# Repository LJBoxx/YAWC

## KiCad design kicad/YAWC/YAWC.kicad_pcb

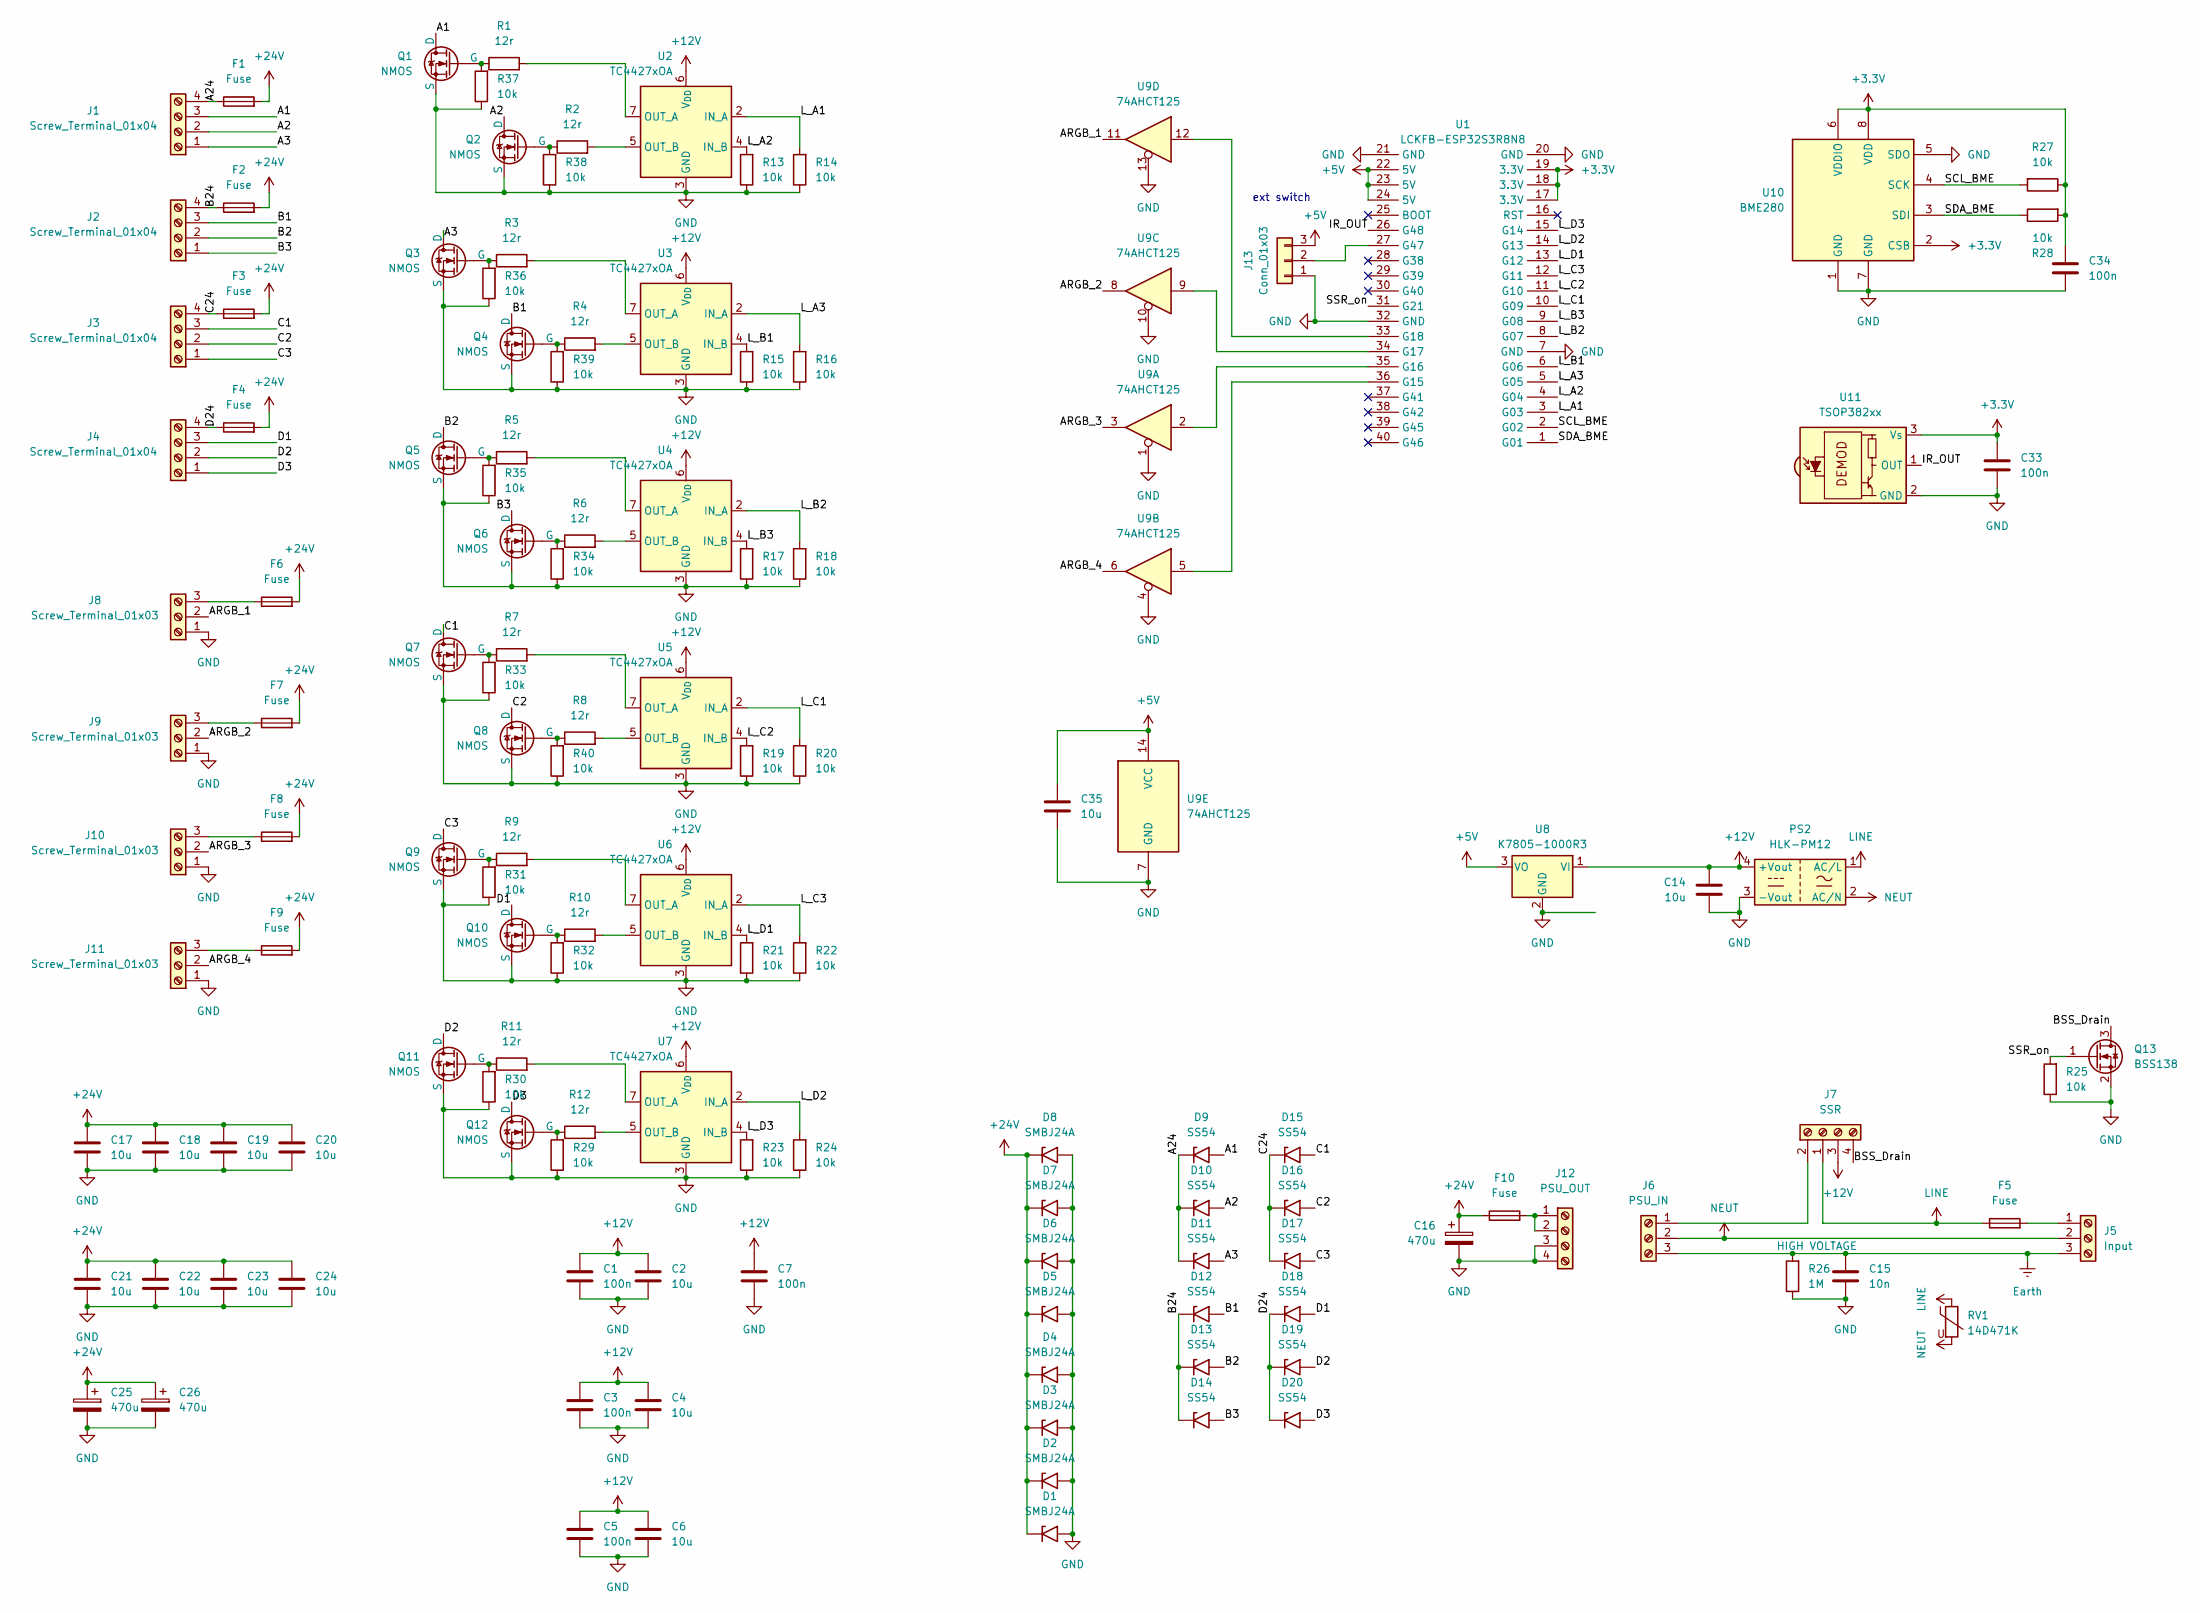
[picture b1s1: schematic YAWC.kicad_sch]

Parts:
C1, C3, C5, C7, C33, C34: 100n; C_0603_1608Metric; LCSC C1591
C2, C4, C6, C14, C17, C18, C19, C20, C21, C22, C23, C24, C35: 10u; C_1210_3225Metric; LCSC C138687
C15: 10n; C_Rect_L13.0mm_W4.0mm_P10.00mm_FKS3_FKP3_MKS4; LCSC C428926
C16, C25, C26: 470u; CP_Radial_D10.0mm_P5.00mm; LCSC C3038120
D1, D2, D3, D4, D5, D6, D7, D8: SMBJ24A; D_SMB; LCSC C224017
D9, D10, D11, D12, D13, D14, D15, D16, D17, D18, D19, D20: SS54; D_SMB; LCSC C22452
F1, F2, F3, F4, F6, F7, F8, F9, F10: Fuse; FUSE-TH_4P-L16.0-W6.7; LCSC C19727305
F5: Fuse; Fuse_Bourns_MF-SM_9.5x6.71mm; LCSC C108518
J1, J2, J3, J4: Screw_Terminal_01x04; TerminalBlock_bornier-4_P5.08mm; LCSC C2915641
J5: Input; TerminalBlock_bornier-3_P5.08mm; LCSC C72334
J6: PSU_IN; TerminalBlock_bornier-3_P5.08mm; LCSC C72334
J7: SSR; TerminalBlock_bornier-4_P5.08mm; LCSC C2915641
J8, J9, J10, J11: Screw_Terminal_01x03; TerminalBlock_bornier-3_P5.08mm; LCSC C72334
J12: PSU_OUT; TerminalBlock_bornier-4_P5.08mm; LCSC C2915641
J13: Conn_01x03; PinHeader_1x03_P2.54mm_Vertical
PS2: HLK-PM12; Converter_ACDC_Hi-Link_HLK-PMxx; LCSC C209905
Q1, Q2, Q3, Q4, Q5, Q6, Q7, Q8, Q9, Q10, Q11, Q12: NMOS; Infineon_PG-HSOF-8-1; LCSC C42403238
Q13: BSS138; SOT-23; LCSC C52895
R1, R2, R3, R4, R5, R6, R7, R8, R9, R10, R11, R12: 12r; R_0603_1608Metric; LCSC C246021
R13, R14, R15, R16, R17, R18, R19, R20, R21, R22, R23, R24, R25, R27, R28, R29, R30, R31, R32, R33, R34, R35, R36, R37, R38, R39, R40: 10k; R_0603_1608Metric; LCSC C15401
R26: 1M; R_1210_3225Metric; LCSC C2933801
RV1: 14D471K; RV_Disc_D12mm_W5.4mm_P7.5mm; LCSC C2761683
U1: LCKFB-ESP32S3R8N8; DIP-40_L20.32-W51.66-P2.54-LS15.24; LCSC C20626143
U2, U3, U4, U5, U6, U7: TC4427xOA; SOIC-8_3.9x4.9mm_P1.27mm; LCSC C20551
U8: K7805-1000R3; TO-220-3_Vertical; LCSC C2992391
U9: 74AHCT125; SOIC-14_3.9x8.7mm_P1.27mm; LCSC C554502
U10: BME280; Bosch_LGA-8_2.5x2.5mm_P0.65mm_ClockwisePinNumbering; LCSC C92489
U11: TSOP382xx; Vishay_MINICAST-3Pin; LCSC C141632

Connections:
+3.3V: C33.1, C34.1, R27.1, R28.2, U1.17 (3.3V), U1.18 (3.3V), U1.19 (3.3V), U10.2 (CSB), U10.6 (VDDIO), U10.8 (VDD), U11.3 (Vs)
+5V: C35.1, J13.3, U1.22 (5V), U1.23 (5V), U1.24 (5V), U8.3 (VO), U9.14 (VCC)
+12V: C1.1, C2.1, C3.1, C4.1, C5.1, C6.1, C7.1, C14.1, J7.3, PS2.4 (+Vout), U2.6 (V_{DD}), U3.6 (V_{DD}), U4.6 (V_{DD}), U5.6 (V_{DD}), U6.6 (V_{DD}), U7.6 (V_{DD}), U8.1 (VI)
+24V: C16.1, C17.1, C18.1, C19.1, C20.1, C21.1, C22.1, C23.1, C24.1, C25.1, C26.1, D1.1 (A1), D2.1 (A1), D3.1 (A1), D4.1 (A1), D5.1 (A1), D6.1 (A1), D7.1 (A1), D8.1 (A1), F1.2, F2.2, F3.2, F4.2, F6.2, F7.2, F8.2, F9.2, F10.1
/A1: D9.2 (A2), J1.3, Q1.1 (D)
/A2: D10.2 (A2), J1.2, Q2.1 (D)
/A3: D11.2 (A2), J1.1, Q3.1 (D)
/A24: D9.1 (A1), D10.1 (A1), D11.1 (A1), F1.1, J1.4
/ARGB_1: J8.2, U9.11
/ARGB_2: J9.2, U9.8
/ARGB_3: J10.2, U9.3
/ARGB_4: J11.2, U9.6
/B1: D12.2 (A2), J2.3, Q4.1 (D)
/B2: D13.2 (A2), J2.2, Q5.1 (D)
/B3: D14.2 (A2), J2.1, Q6.1 (D)
/B24: D12.1 (A1), D13.1 (A1), D14.1 (A1), F2.1, J2.4
/BSS_Drain: J7.4, Q13.3 (D)
/C1: D15.2 (A2), J3.3, Q7.1 (D)
/C2: D16.2 (A2), J3.2, Q8.1 (D)
/C3: D17.2 (A2), J3.1, Q9.1 (D)
/C24: D15.1 (A1), D16.1 (A1), D17.1 (A1), F3.1, J3.4
/D1: D18.2 (A2), J4.3, Q10.1 (D)
/D2: D19.2 (A2), J4.2, Q11.1 (D)
/D3: D20.2 (A2), J4.1, Q12.1 (D)
/D24: D18.1 (A1), D19.1 (A1), D20.1 (A1), F4.1, J4.4
/IR_OUT: U1.26 (G48), U11.1 (OUT)
/L_A1: R14.2, U1.3 (G03), U2.2 (IN_A)
/L_A2: R13.2, U1.4 (G04), U2.4 (IN_B)
/L_A3: R16.2, U1.5 (G05), U3.2 (IN_A)
/L_B1: R15.2, U1.6 (G06), U3.4 (IN_B)
/L_B2: R18.2, U1.8 (G07), U4.2 (IN_A)
/L_B3: R17.2, U1.9 (G08), U4.4 (IN_B)
/L_C1: R20.2, U1.10 (G09), U5.2 (IN_A)
/L_C2: R19.2, U1.11 (G10), U5.4 (IN_B)
/L_C3: R22.2, U1.12 (G11), U6.2 (IN_A)
/L_D1: R21.2, U1.13 (G12), U6.4 (IN_B)
/L_D2: R24.2, U1.14 (G13), U7.2 (IN_A)
/L_D3: R23.2, U1.15 (G14), U7.4 (IN_B)
/SCL_BME: R27.2, U1.2 (G02), U10.4 (SCK)
/SDA_BME: R28.1, U1.1 (G01), U10.3 (SDI)
/SSR_on: Q13.1 (G), R25.2, U1.31 (G21)
Earth: C15.1, J5.3, J6.3, R26.2
GND: C1.2, C2.2, C3.2, C4.2, C5.2, C6.2, C7.2, C14.2, C15.2, C16.2, C17.2, C18.2, C19.2, C20.2, C21.2, C22.2, C23.2, C24.2, C25.2, C26.2, C33.2, C34.2, C35.2, D1.2 (A2), D2.2 (A2), D3.2 (A2), D4.2 (A2), D5.2 (A2), D6.2 (A2), D7.2 (A2), D8.2 (A2), J8.1, J9.1, J10.1, J11.1, J12.3, J12.4, J13.1, PS2.3 (-Vout), Q1.3 (S), Q2.3 (S), Q3.3 (S), Q4.3 (S), Q5.3 (S), Q6.3 (S), Q7.3 (S), Q8.3 (S), Q9.3 (S), Q10.3 (S), Q11.3 (S), Q12.3 (S), Q13.2 (S), R13.1, R14.1, R15.1, R16.1, R17.1, R18.1, R19.1, R20.1, R21.1, R22.1, R23.1, R24.1, R25.1, R26.1, R29.1, R30.1, R31.1, R32.1, R33.1, R34.1, R35.1, R36.1, R37.1, R38.1, R39.1, R40.1, U1.7 (GND), U1.20 (GND), U1.21 (GND), U1.32 (GND), U2.3 (GND), U3.3 (GND), U4.3 (GND), U5.3 (GND), U6.3 (GND), U7.3 (GND), U8.2 (GND), U9.1, U9.4, U9.7 (GND), U9.10, U9.13, U10.1 (GND), U10.5 (SDO), U10.7 (GND), U11.2 (GND)
LINE: F5.1, J7.1, PS2.1 (AC/L), RV1.1
NEUT: J5.2, J6.2, PS2.2 (AC/N), RV1.2
unnamed: F5.2, J5.1
unnamed: J6.1, J7.2
unnamed: F6.1, J8.3
unnamed: F7.1, J9.3
unnamed: F8.1, J10.3
unnamed: F9.1, J11.3
unnamed: F10.2, J12.1, J12.2
unnamed: J13.2, U1.27 (G47)
unnamed: Q1.2 (G), R1.1, R37.2
unnamed: Q2.2 (G), R2.1, R38.2
unnamed: Q3.2 (G), R3.1, R36.2
unnamed: Q4.2 (G), R4.1, R39.2
unnamed: Q5.2 (G), R5.1, R35.2
unnamed: Q6.2 (G), R6.1, R34.2
unnamed: Q7.2 (G), R7.1, R33.2
unnamed: Q8.2 (G), R8.1, R40.2
unnamed: Q9.2 (G), R9.1, R31.2
unnamed: Q10.2 (G), R10.1, R32.2
unnamed: Q11.2 (G), R11.1, R30.2
unnamed: Q12.2 (G), R12.1, R29.2
unnamed: U1.36 (G15), U9.5
unnamed: U1.35 (G16), U9.2
unnamed: U1.34 (G17), U9.9
unnamed: U1.33 (G18), U9.12
unnamed: R1.2, U2.7 (OUT_A)
unnamed: R2.2, U2.5 (OUT_B)
unnamed: R3.2, U3.7 (OUT_A)
unnamed: R4.2, U3.5 (OUT_B)
unnamed: R5.2, U4.7 (OUT_A)
unnamed: R6.2, U4.5 (OUT_B)
unnamed: R7.2, U5.7 (OUT_A)
unnamed: R8.2, U5.5 (OUT_B)
unnamed: R9.2, U6.7 (OUT_A)
unnamed: R10.2, U6.5 (OUT_B)
unnamed: R11.2, U7.7 (OUT_A)
unnamed: R12.2, U7.5 (OUT_B)

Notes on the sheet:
ext switch

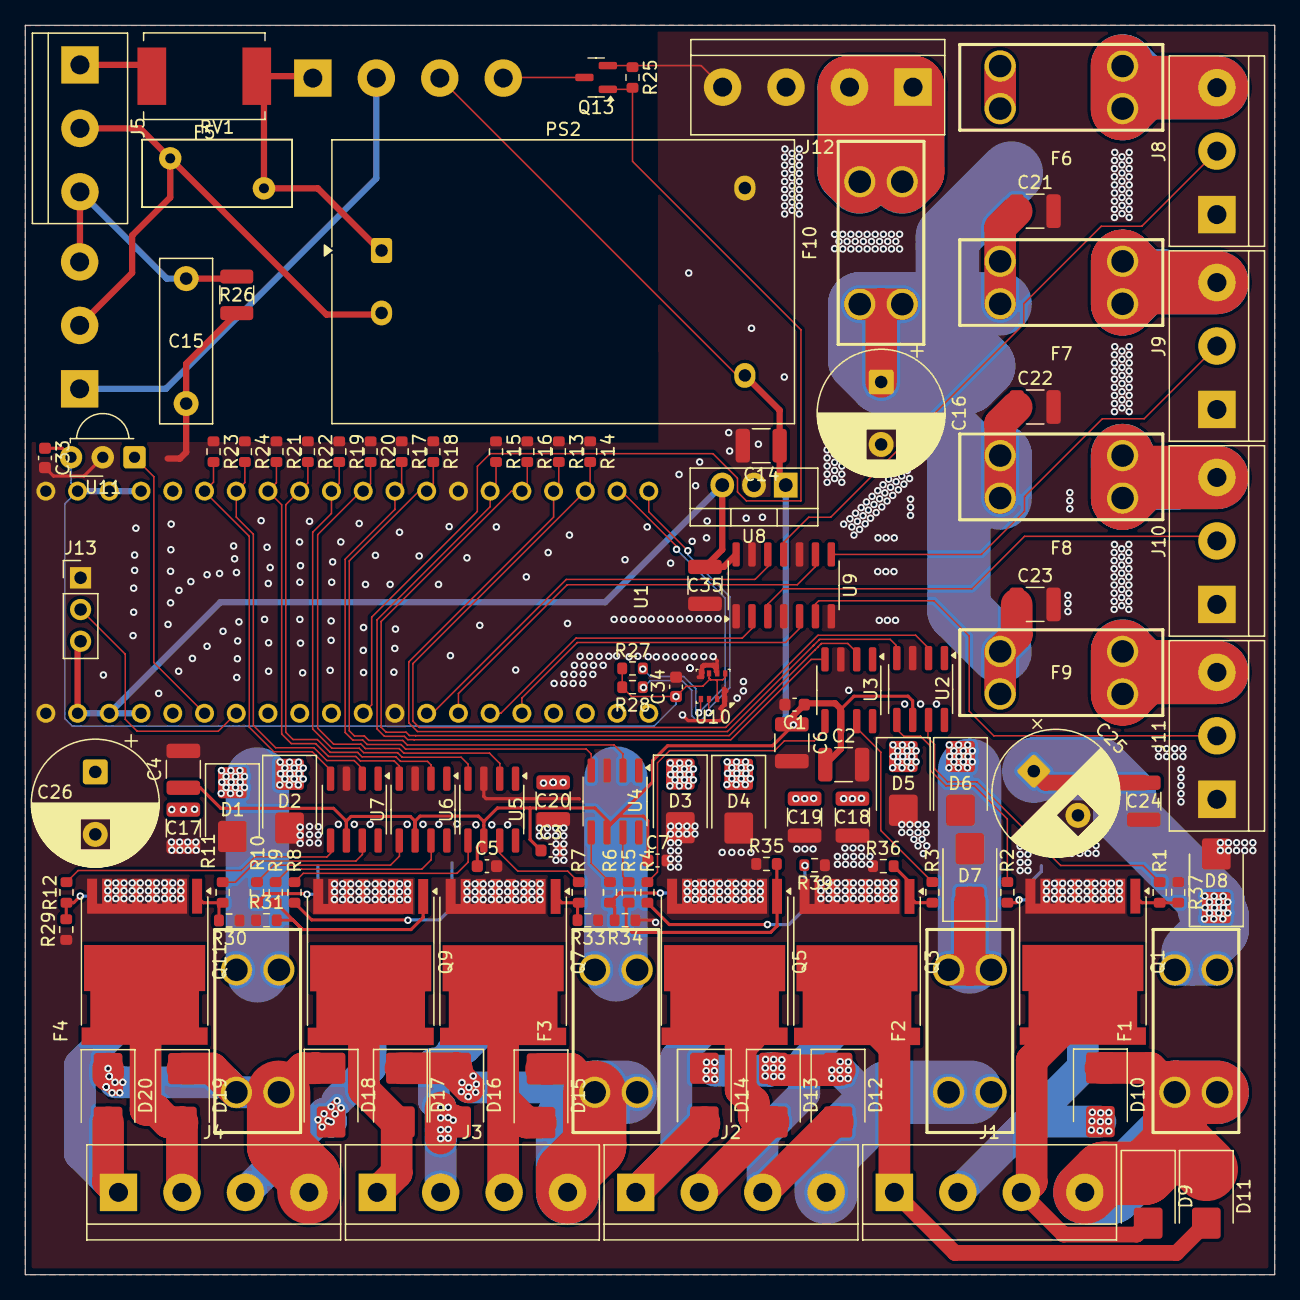
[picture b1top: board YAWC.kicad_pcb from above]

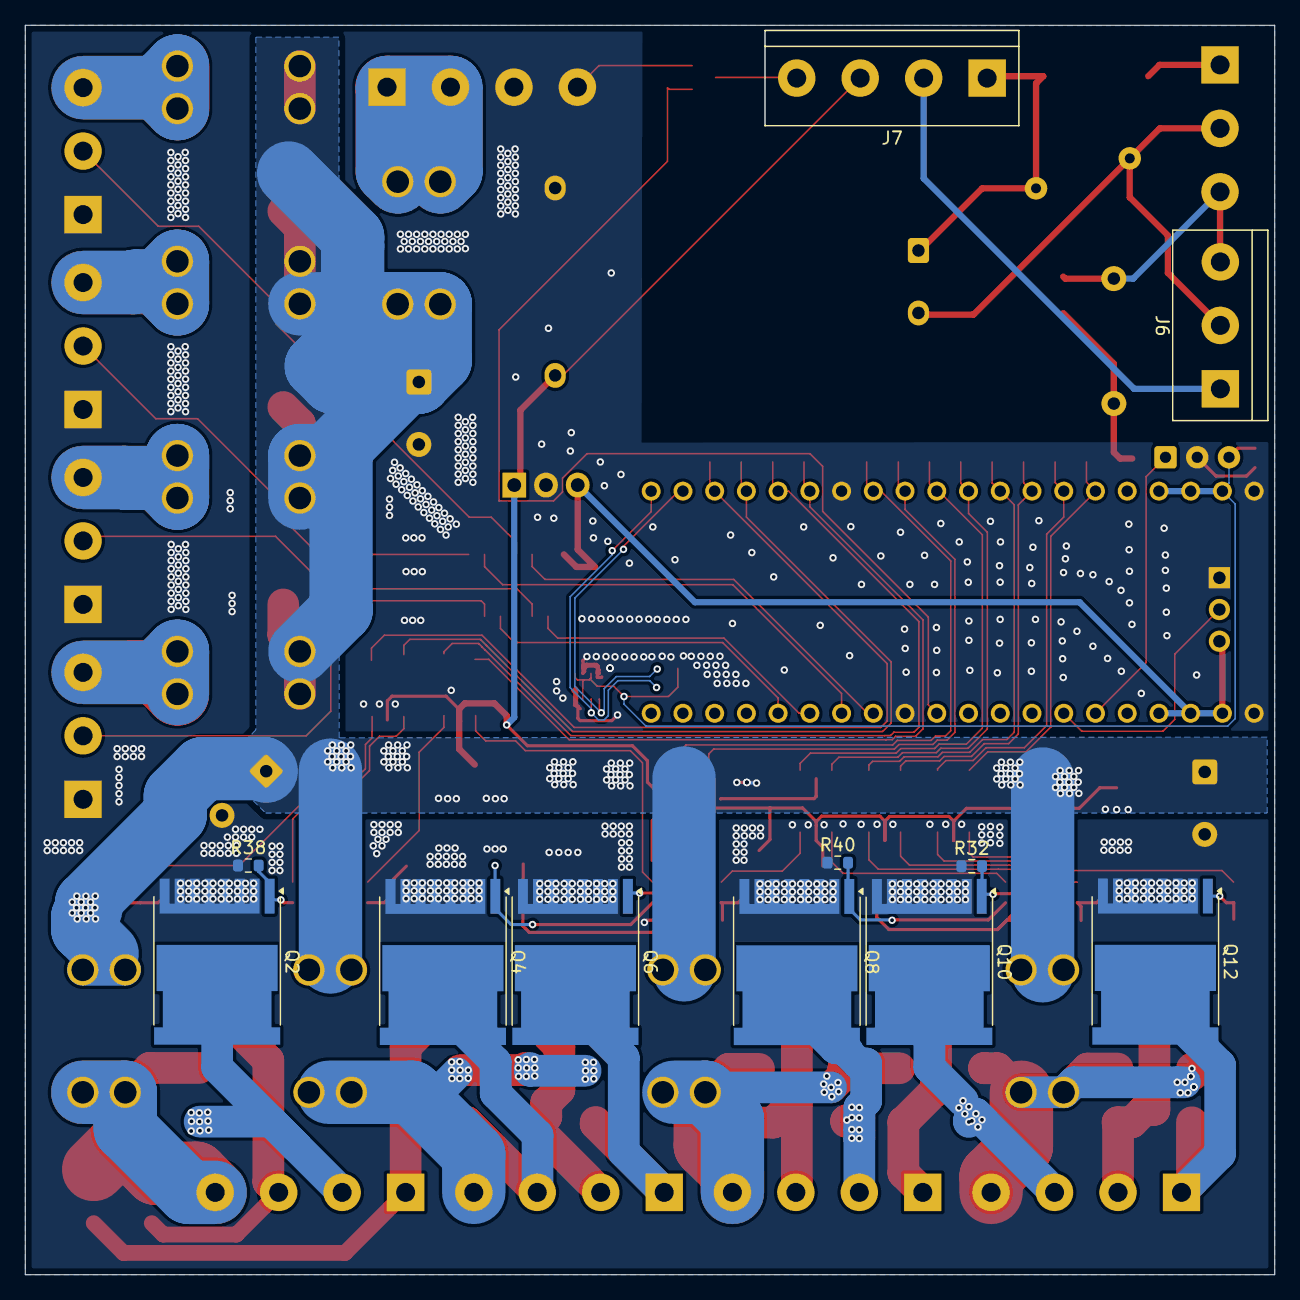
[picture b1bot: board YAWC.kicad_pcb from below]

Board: 2 copper layers, 100.0 x 100.0 mm, 132 parts (11 on the bottom side), 81 nets.

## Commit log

2025-12-24 Kicad Schematic
    Worked on the kicad schematic a lot today. Next part assignment to finish and pcb routing.
2025-12-25 parts assign
    finished part assignement.
2025-12-28 finished pcb routing
    basically finished i suppose ?
